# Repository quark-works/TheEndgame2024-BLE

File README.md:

# This is amodified version of THE ENDGAME keyboard to make it wireless
 This works by using a SuperMini NRF52840 or a nice!nano. Sadly, there's not solution with castellated holes so the soldering is a little bit... special. Here are some pictures of the board:

## CASE

There's an updated version of the case with a slot for a battery, please measure which battery will fit as it is a pretty small opening. ZMK is pretty power efficient os that's not an issue.

## FIRMWARE

Included is a precompiled firmware ZMK Studio ready as well as the source I've used.
Additionally there is a VIAL firmware if you are more familiar with that and do not need wireless capability. However you can only use this if you have a pro-micro rp2040 mcu installed on your pcb. Be aware that pinout is not the same as with SuperMini NRF52840 or nice!nano.

## MY BUILD

## Caveats:
- Soldering is a little on the harder side. You gotta align the board and feed enough solder so it melts and attaches both the pads on the PCB and the pads on the micro.
- I don't fully like how close the battery pads are. Be careful when you solder the batter. My recommendarion is: Solder one pad, add tape, then solder the other pad.
- I'd love to remake this board to have everything preassembled but this version works well enough. If there's enough interest I might just do it.

## Following is the original GitHub repo content

## Who the F... is Alice ##

Inspired by the legendary TGR Alice, the ENDGAME pays homage to a true classic. While it might not claim the top spot for ergonomics, it's design speaks for itself an iconic piece you’ll want to show off, even if it takes a bit of time for your fingers to adjust.

This low profile keyboard is built for high performance typing. Its slightly staggered layout works beautifully for both ergonomic beginners and experienced users. The unique bottomless top mount design makes it incredibly slim, lightweight, and perfect for those on the move.

## Everything You Need, All In One Place ##

Get the entire kit from KeebSupply, a trusted vendor with affordable international shipping. It’s your one stop shop for everything you need highly recommended! [Buy here](https://keeb.supply/products/endgame) 

For an excellent build guide, check out this fantastic resource from KeebSupply. I haven’t had the time to create my own guide (and honestly, I couldn’t top this one). Big thanks to @KeebSupply! [Build Guide and Supplies](https://docs.keeb.supply/endgame/) 

## PARTS LIST PCB ##

- 1x The Endgame PCB             [Gerber Files](https://github.com/OldMan6955/TheEndgame2024/tree/main/001%20PCB) 

There are now two versions of the PCB:
1.	COPPER Version:
In this version, all design elements are on the copper and mask layers. I used this version to create my prototypes. However, this version has longer loading times, and the Gerber files currently don’t work with JLCPCB. (I’d greatly appreciate any help with troubleshooting this issue.)
2.	SILKSCREEN Version:
This version is untested. All design elements have been moved to the silkscreen layer, making it much more performant on less powerful PCs. The Gerber files display correctly on JLCPCB but have not yet been tested.
Please always test the files yourself to rule out potential errors. Thank you!

- 36x Choc v1 Hotswap Sockets    [buy here](https://www.aliexpress.com/item/1005004916925259.html?) 
- 36x Diodes SOD123 / 1N4148W T4 [buy here](https://de.aliexpress.com/item/1005004309686841.html?) 
- 1x Waveshare RP2040 UGLY AF    [buy here](https://de.aliexpress.com/item/1005006354505058.html?) 

or get the better looking thingy, highly recommended

- | 01 | 0xCB Gemini             [buy here](https://keeb.supply/products/0xcb-gemini) |

## PARTS LIST FDM CASE ##

- 4x M3 6mm countersunk          [buy here](https://de.aliexpress.com/item/4001199728978.html) 
- 4x M3 5mm flathead             [buy here](https://de.aliexpress.com/item/1005005069968742.html) 

You can choose either countersunk or flathead screws both work well. Countersunk screws automatically align the PCB, while flathead screws allow you to manually align and adjust as needed.
The hole for the heat inserts is 4mm deep, and the PCB is 1.6mm thick, so 5mm screws are a perfect fit. Just double-check how the screw length is measured, as this can vary.

- 4x M3 D4.6mm L3mm Heatinsert   [buy here](https://de.aliexpress.com/item/4000232858343.html) 
- 12x M3 D6.6mm grommet black     [buy here](https://de.aliexpress.com/item/4000712868621.html) 

You’ll need 4 grommets if you’re aiming for a bit of flex or bounce, but you can use up to 12 depending on your preference. They work perfectly as feet and provide excellent grip on my desk. Alternatively, bumpons are a great option too.

## SWITCHES AND KEYCAPS ##

Switches

I highly recommend the Choc v1 Silent switches, such as [Nocturnal](https://keeb.supply/products/nocturnal-low-profile-switches) or [Twilights](https://keeb.supply/products/twilight-low-profile-switches). If you prefer heavier springs and a bit of tactile feedback but don’t need silence, [Sunset](https://keeb.supply/products/sunset-low-profile-switches) switches are an excellent choice. As for the rest of the Choc v1 lineup, I wouldn’t bother—they’re not worth considering.

Keycaps

My go-to choice is standard [MBK](https://keeb.supply/products/mbk-keycaps) keycaps, but personal preference always plays a role. For your setup, you’ll need:

- 30x 1U keycaps for the alpha keys (or 28x 1U and 2x 1U homing keycaps)
- 4x 1.5U and 2x 1U convex keycaps for the bottom row

Check with your local vendor, they’re in stock almost everywhere these days. A great way to test switches and keycaps is by attending meetups, there might be an active community near you.

## FIRMWARE - QMK AND VIAL ##

The firmware, expertly created by [dreipunkteinsvier](https://github.com/dreipunkteinsvier), is available for download: [Get it here](https://github.com/OldMan6955/TheEndgame2024/tree/main/003%20FIRMWARE) 
Huge thanks to him, I’d have been completely lost without his help!

## DISCLAIMER ##

This keyboard is an open-source project, and all files are provided free of charge for personal use. While these files have been tested and worked for me, they are provided without any guarantees or warranties of any kind.

By using these files, you agree to take full responsibility for verifying their suitability for your needs. Any orders, modifications, or reproductions made based on these files are done at your own risk. I am not liable for any issues, damages, or losses that may arise from the use of these files or the assembly of the keyboard.

Please ensure you carefully review all files and specifications before proceeding. Thank you for understanding!

## RANDOM PEOPLE I KNOW ##

After three years of development and collaboration with contributors from around the world, the ENDGAME is more than just a keyboard it’s the result of a shared journey, a community driven effort that reflects the passion and creativity of everyone involved.

- [Marco "Bob"](https://github.com/GroooveBob) - for answering all my dumb questions 24/7
- [dreipunkteinsvier](https://github.com/dreipunkteinsvier) - firmware and stupid github
- [bubbleology](https://github.com/bubbleology) - inspiration, CAD and emotional support
- [GEIST](https://github.com/GEIGEIGEIST) - can't remember what, but we talked about stuff back in the days RIP
- MY WIFE - for reasons
- and many more

To all who contributed thank you. Enjoy the journey, and have fun exploring what this keyboard can do!

## PICTURES ##

## ONLY FANS ##

While this project is free and open source, I truly appreciate your support. If you'd like to contribute, feel free to leave a tip via Ko-fi to help support future projects. Thank you!

## SHARE YOUR BUILDS ##

Do you love your ENDGAME? I’d love to see your builds! Join the Discord community to share pictures of your keyboards and chat with fellow enthusiasts.
Just a heads-up: I can’t help with technical issues or soldering nightmares because I’m still learning myself. So, please don’t ask me for help with that!

## FINAL WISDOM ##

    "The worst thing that can happen is someone calling me a keyboard designer."
    -OLDMAN6955

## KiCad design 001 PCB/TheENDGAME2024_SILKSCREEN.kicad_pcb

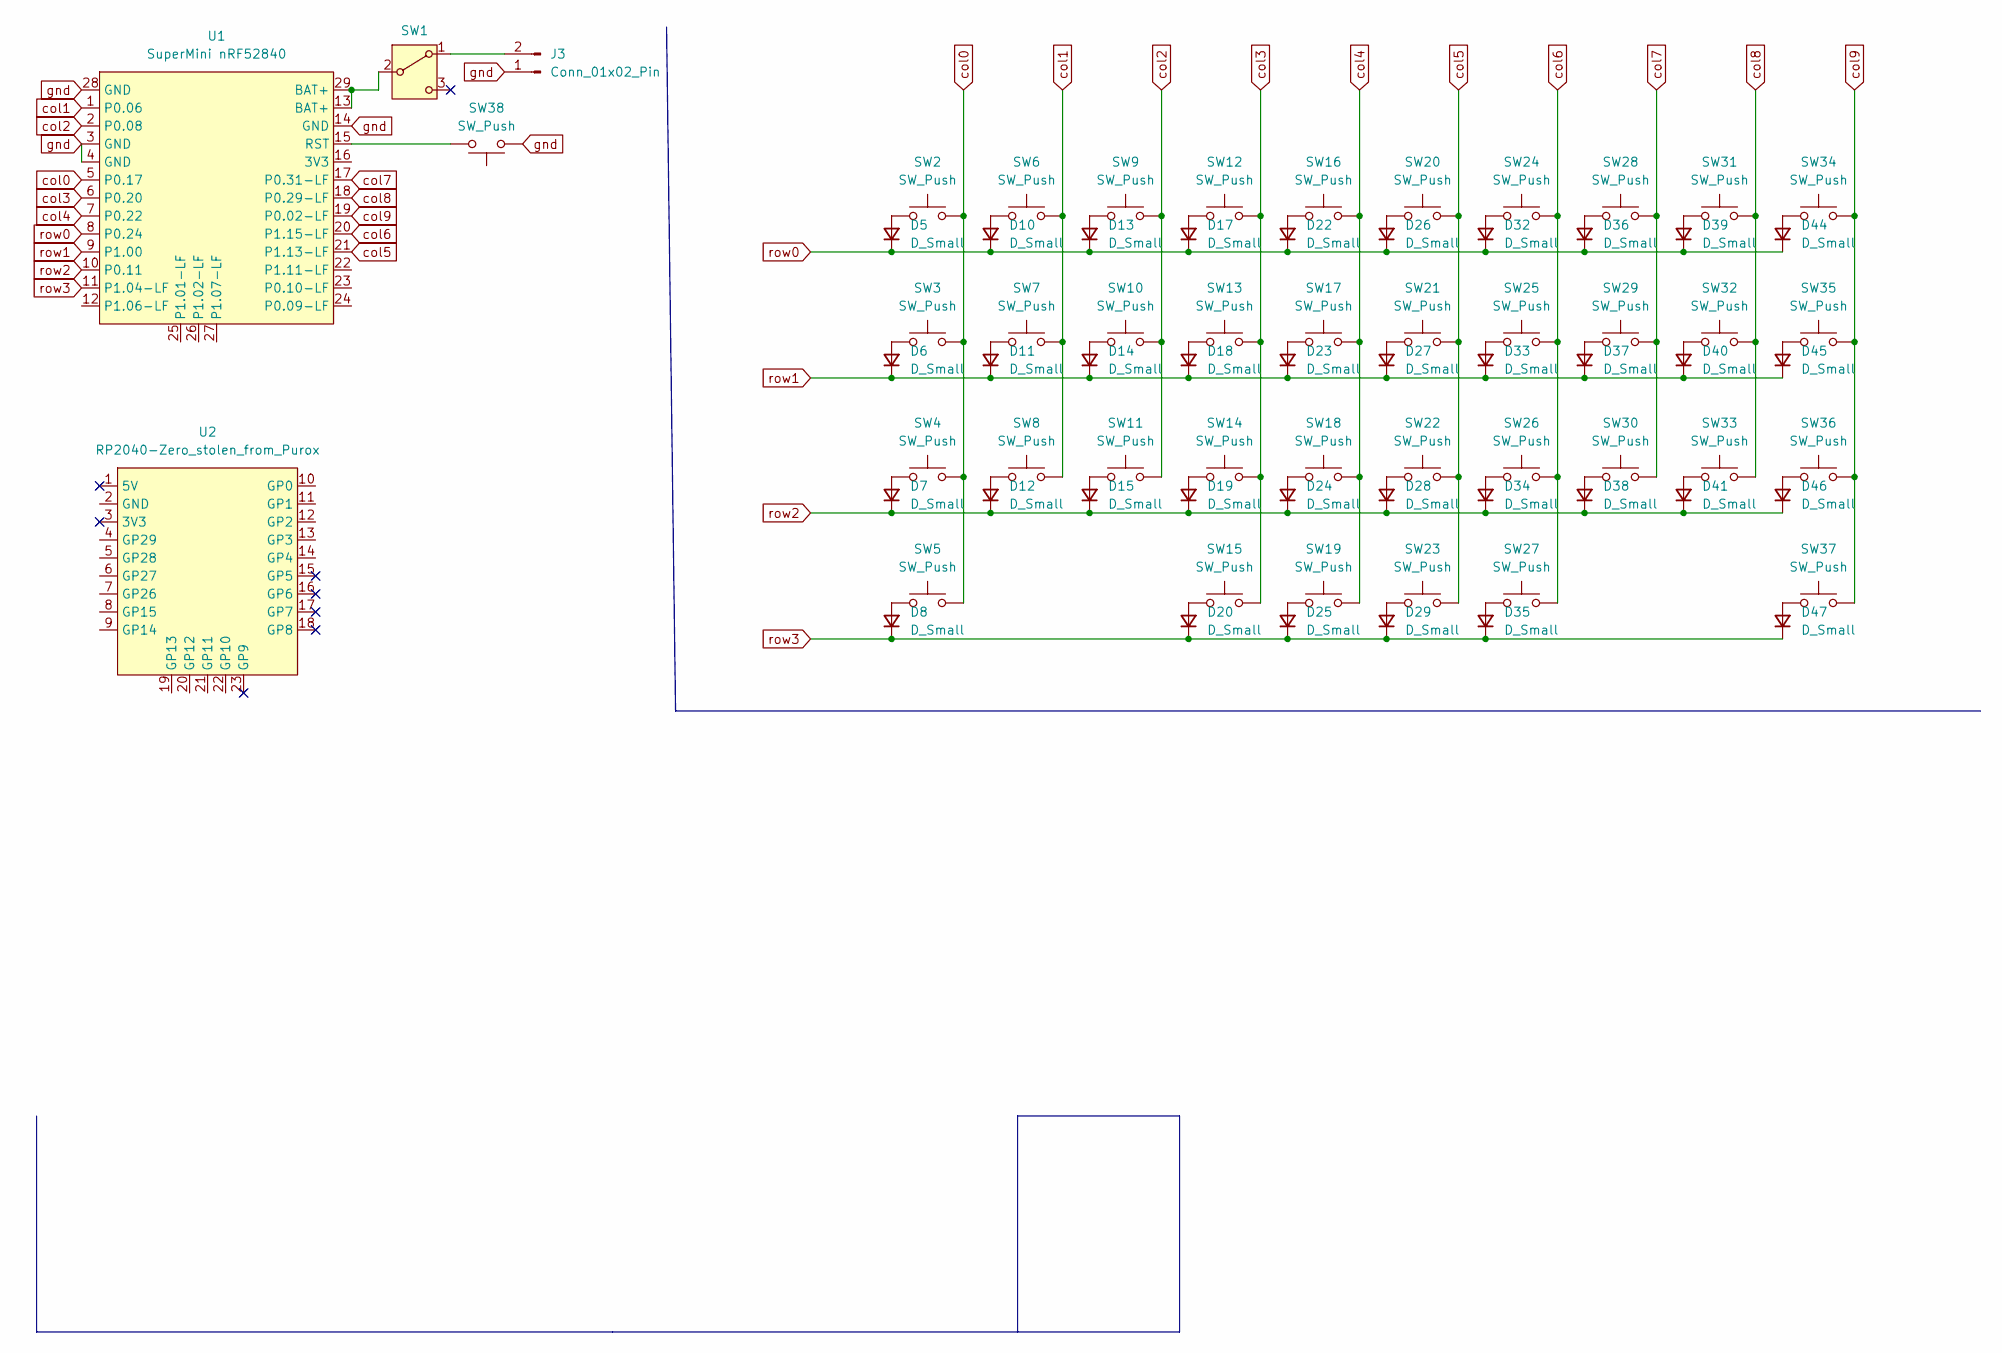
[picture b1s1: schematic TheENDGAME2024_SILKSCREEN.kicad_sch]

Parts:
D5, D6, D7, D8, D10, D11, D12, D13, D14, D15, D17, D18, D19, D20, D22, D23, D24, D25, D26, D27, D28, D29, D32, D33, D34, D35, D36, D37, D38, D39, D40, D41, D44, D45, D46, D47: D_Small; Diode_SOD123 filets triangle
J3: Conn_01x02_Pin; Molex_PicoBlade_53048-0210_1x02_P1.25mm_Horizontal
SW1: SW_SPDT; SW_SPDT_PCM12
SW2, SW3, SW4, SW6, SW7, SW8, SW9, SW10, SW11, SW12, SW13, SW14, SW15, SW16, SW17, SW18, SW20, SW21, SW22, SW24, SW25, SW26, SW27, SW28, SW29, SW30, SW31, SW32, SW33, SW34, SW35, SW36: SW_Push; SW_choc_v1_HSxSolder_1u_filets_MBK_blk fixxed flipped solde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
SW5, SW19, SW23, SW37: SW_Push; SW_choc_v1_HSxSolder_1.5u_filets_MBK_blk fixxed flipped sol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
SW38: SW_Push; SW_SPST_SKQG_WithStem
U1: SuperMini nRF52840; SuperMini_nRF52840_AH_USBup
U2: RP2040-Zero_stolen_from_Purox; RP2040 Zero stolen from Purox bottom facing up 3d model v3

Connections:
unnamed: D5.2 (A), SW2.1
unnamed: D6.2 (A), SW3.1
unnamed: D7.2 (A), SW4.1
unnamed: D8.2 (A), SW5.1
unnamed: D10.2 (A), SW6.1
unnamed: D11.2 (A), SW7.1
unnamed: D12.2 (A), SW8.1
unnamed: D13.2 (A), SW9.1
unnamed: D14.2 (A), SW10.1
unnamed: D15.2 (A), SW11.1
unnamed: D17.2 (A), SW12.1
unnamed: D18.2 (A), SW13.1
unnamed: D19.2 (A), SW14.1
unnamed: D20.2 (A), SW15.1
unnamed: D22.2 (A), SW16.1
unnamed: D23.2 (A), SW17.1
unnamed: D24.2 (A), SW18.1
unnamed: D25.2 (A), SW19.1
unnamed: D26.2 (A), SW20.1
unnamed: D27.2 (A), SW21.1
unnamed: D28.2 (A), SW22.1
unnamed: D29.2 (A), SW23.1
unnamed: D32.2 (A), SW24.1
unnamed: D33.2 (A), SW25.1
unnamed: D34.2 (A), SW26.1
unnamed: D35.2 (A), SW27.1
unnamed: D36.2 (A), SW28.1
unnamed: D37.2 (A), SW29.1
unnamed: D38.2 (A), SW30.1
unnamed: D39.2 (A), SW31.1
unnamed: D40.2 (A), SW32.1
unnamed: D41.2 (A), SW33.1
unnamed: D44.2 (A), SW34.1
unnamed: D45.2 (A), SW35.1
unnamed: D46.2 (A), SW36.1
unnamed: D47.2 (A), SW37.1
unnamed: J3.2, SW1.1 (A)
unnamed: SW1.2 (B), U1.13 (BAT+), U1.29 (BAT+)
unnamed: SW38.2, U1.15 (RST)
col0: SW2.2, SW3.2, SW4.2, SW5.2, U1.5 (P0.17)
col1: SW6.2, SW7.2, SW8.2, U1.1 (P0.06)
col2: SW9.2, SW10.2, SW11.2, U1.2 (P0.08)
col3: SW12.2, SW13.2, SW14.2, SW15.2, U1.6 (P0.20)
col4: SW16.2, SW17.2, SW18.2, SW19.2, U1.7 (P0.22)
col5: SW20.2, SW21.2, SW22.2, SW23.2, U1.21 (P1.13-LF)
col6: SW24.2, SW25.2, SW26.2, SW27.2, U1.20 (P1.15-LF)
col7: SW28.2, SW29.2, SW30.2, U1.17 (P0.31-LF)
col8: SW31.2, SW32.2, SW33.2, U1.18 (P0.29-LF)
col9: SW34.2, SW35.2, SW36.2, SW37.2, U1.19 (P0.02-LF)
gnd: J3.1, SW38.1, U1.3 (GND), U1.4 (GND), U1.14 (GND), U1.28 (GND)
row0: D5.1 (K), D10.1 (K), D13.1 (K), D17.1 (K), D22.1 (K), D26.1 (K), D32.1 (K), D36.1 (K), D39.1 (K), D44.1 (K), U1.8 (P0.24)
row1: D6.1 (K), D11.1 (K), D14.1 (K), D18.1 (K), D23.1 (K), D27.1 (K), D33.1 (K), D37.1 (K), D40.1 (K), D45.1 (K), U1.9 (P1.00)
row2: D7.1 (K), D12.1 (K), D15.1 (K), D19.1 (K), D24.1 (K), D28.1 (K), D34.1 (K), D38.1 (K), D41.1 (K), D46.1 (K), U1.10 (P0.11)
row3: D8.1 (K), D20.1 (K), D25.1 (K), D29.1 (K), D35.1 (K), D47.1 (K), U1.11 (P1.04-LF)

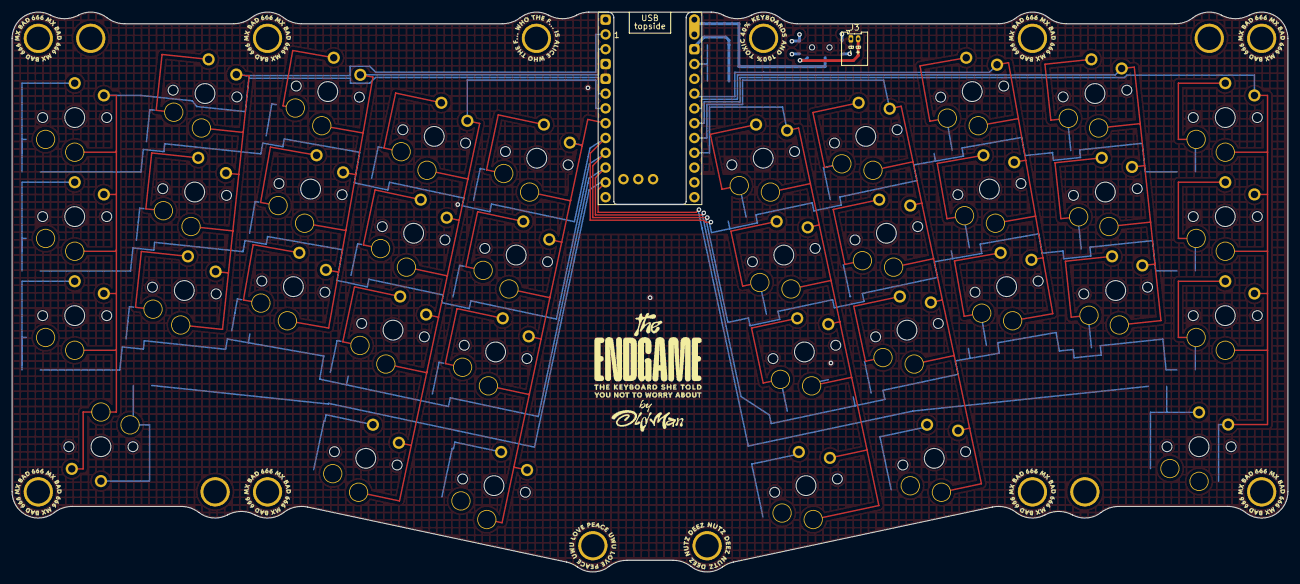
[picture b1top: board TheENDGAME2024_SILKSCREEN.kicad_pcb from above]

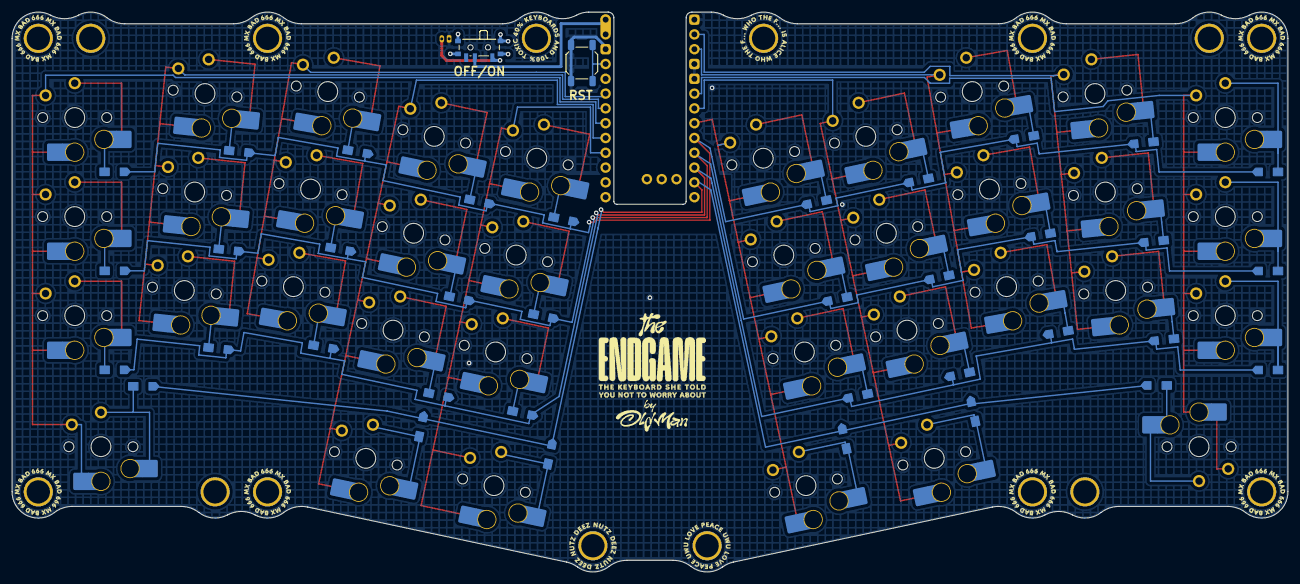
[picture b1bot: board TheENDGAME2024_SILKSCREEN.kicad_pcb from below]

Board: 2 copper layers, 219.0 x 96.1 mm, 76 parts (74 on the bottom side), 54 nets.

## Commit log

2025-10-09 Add vial support for rp2040 promicro mcu
